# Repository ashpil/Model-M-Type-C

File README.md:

# Model M Type C
This is a project with the simple goal of recreating the old IBM Model M keyboard controller with modern technologies in mind.

## Motivation
Although the IBM Model M is perhaps the most well-known and popular of old keyboards, it isn't equipped with some modern ameneties we have grown used to enjoying. Key features that the Model M lacks are Windows and Media keys(or, broader, firmware-level repogramability), as well as a hotswappable connection with a modern interface. This controller is designed to bring 21st century features to a 20th century keyboard.

## Goals
- Native USB C
- Hotswappable
- Fully configurable with QMK compatibility
- Less power draw
- Complete reversability

## Usage
Note: If your Model M has two ribbon cables with a 16-12 split rather than the three connectors with 16-8-4 split, see [this](https://github.com/ashpil/Model-M-Type-C-Controller/issues/2) issue.

1. Print the board either using a cheap foreign service such as [JLCPBC](https://jlcpcb.com/ "JLCPBC") for around $6 + shipping, or a domestic service such as [OSH Park](https://oshpark.com/ "OSH Park") for around $35. Someone also seems to be selling a PCB for this on eBay, which is totally a scam for $47.95. Does make me feel flattered, though.
2. Order the components- [part list](https://www.digikey.com/short/p00t8f "part list") from Digikey. USB-C port needs to be bought elsewhere, I recommend [here](https://keeb.io/products/usb-c-port-12-pin-hro-type-c-31-m-12 "usb c hro female port").  $15 total for components. If your LEDs connect via a ribbon, get [this](https://www.digikey.com/short/p012jt "this") instead of the JST 4 pin connector. I used [this](https://www.amazon.com/gp/product/B01787RB40 "usb c cable") cable as a riser cable to connect the controller's USB C port to the side of the keyboard. Unfortunately, due to size conflicts, this cannot be done without a riser cable if you want the external usb c cable to be detachable. This brings total component cost to $25 without shipping.
3. Put it together. It's possible to solder these SMD components manually with a soldering iron, but if you are able to find a hot air gun or a reflow oven, it'll be significantly easier. Reference the visual BOM to see what goes where.
4. 3D print the [USB-C cable dock](usbcdock.stl "usb c dock"). You can mount this on top of the board for it to look near-native. Attach the riser cable to the dock with some hot glue or epoxy.
4. Connect the ribbon cables and LED wires, and mount the PCB in the same way the old PCB was mounted. Attach the USB-C dock on top of that.
5. Install firmware.

## Firmware
This board is fully compatible with QMK. This is a default QMK configuration, so all you need to do is run this from your QMK directory when you are ready:

	make ashpil/modelm_usbc:default:flash
	
Check [here](https://github.com/qmk/qmk_firmware/tree/master/keyboards/ashpil/modelm_usbc "QMK profile") for details.

Alternatively you can use the [Vial](https://get.vial.today/) firmware. Setup is analogous to QMK, clone the Vial repo and run:
	
	make ashpil/modelm_usbc:vial:flash

## Other

If you have any problems/comments, or find anything that could be improved, please submit issue or a pull request!

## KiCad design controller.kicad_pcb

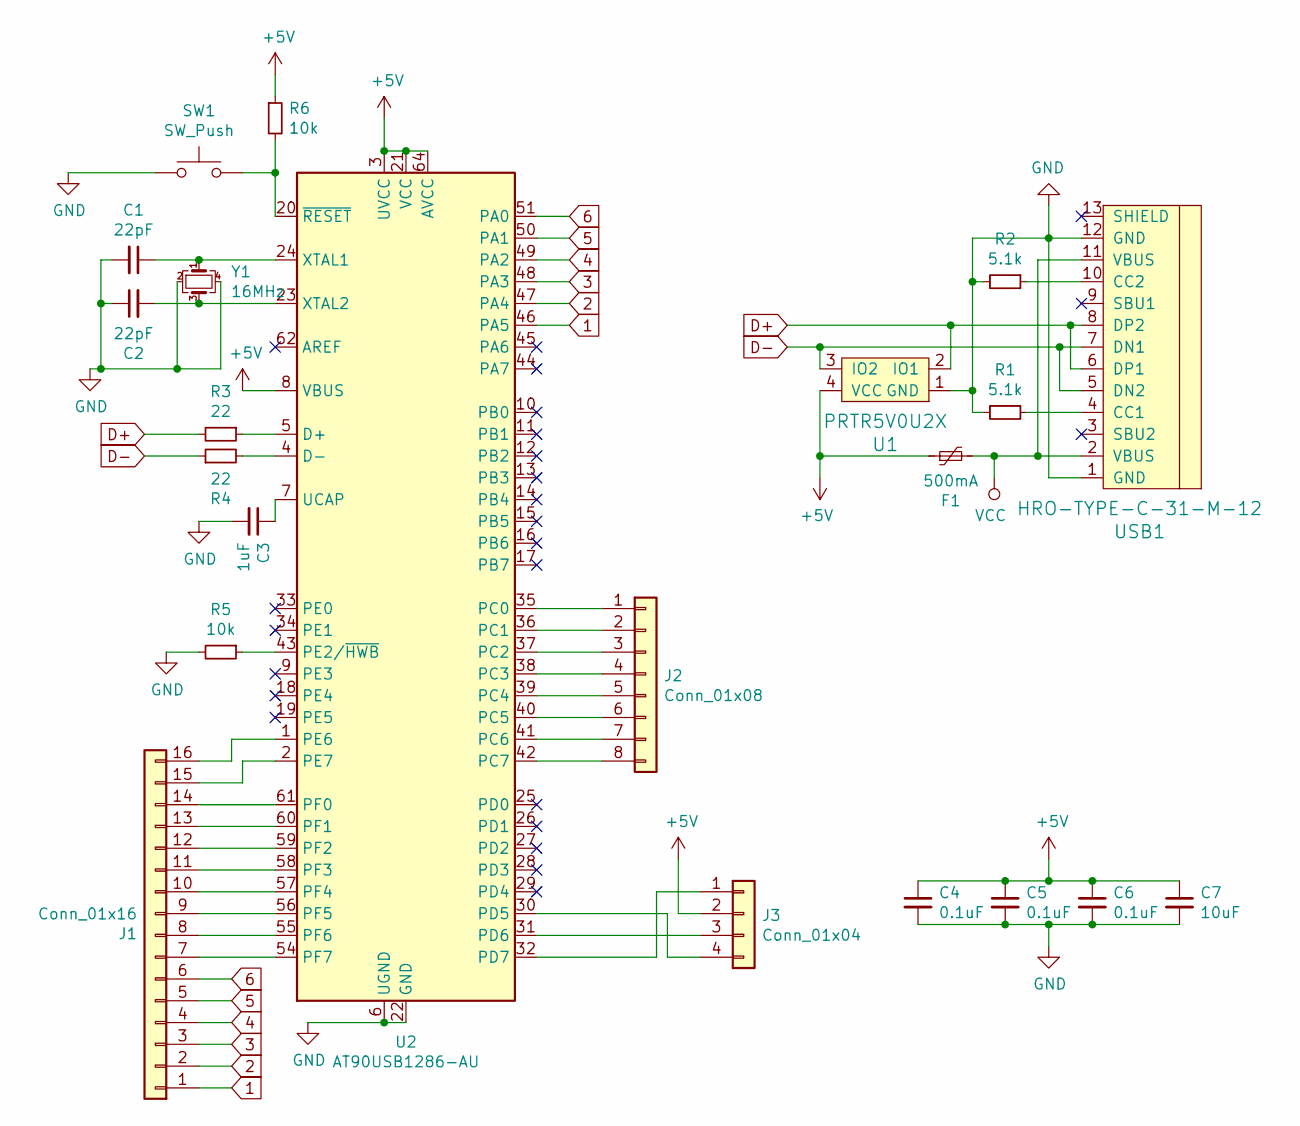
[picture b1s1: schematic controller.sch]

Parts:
C1, C2: 22pF; C_0805_2012Metric
C3: 1uF; C_0805_2012Metric
C4, C5, C6: 0.1uF; C_0805_2012Metric
C7: 10uF; C_0805_2012Metric
F1: 500mA; Fuse_1206_3216Metric
J1: Conn_01x16; PinHeader_1x16_P2.54mm_Vertical
J2: Conn_01x08; PinHeader_1x08_P2.54mm_Vertical
J3: Conn_01x04; PinHeader_1x04_P2.54mm_Vertical
R1, R2: 5.1k; R_0805_2012Metric
R3, R4: 22; R_0805_2012Metric
R5, R6: 10k; R_0805_2012Metric
SW1: SW_Push; SKQG-1155865
U1: PRTR5V0U2X; SOT143B
U2: AT90USB1286-AU; TQFP-64_14x14mm_P0.8mm
USB1: HRO-TYPE-C-31-M-12; HRO-TYPE-C-31-M-12-HandSoldering
Y1: 16MHz; Crystal_SMD_3225-4Pin_3.2x2.5mm

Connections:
1: J1.1, U2.46 (PA5)
2: J1.2, U2.47 (PA4)
3: J1.3, U2.48 (PA3)
4: J1.4, U2.49 (PA2)
5: J1.5, U2.50 (PA1)
6: J1.6, U2.51 (PA0)
+5V: C4.1, C5.1, C6.1, C7.1, F1.1, J3.2, R6.1, U1.4 (VCC), U2.3 (UVCC), U2.8 (VBUS), U2.21 (VCC), U2.52 (VCC), U2.64 (AVCC)
D+: R3.2, U1.2 (IO1), USB1.6 (DP1), USB1.8 (DP2)
D-: R4.1, U1.3 (IO2), USB1.5 (DN2), USB1.7 (DN1)
GND: C1.2, C2.1, C3.2, C4.2, C5.2, C6.2, C7.2, R1.2, R2.2, R5.2, SW1.1, U1.1 (GND), U2.6 (UGND), U2.22 (GND), U2.53 (GND), U2.63 (GND), USB1.1 (GND), USB1.12 (GND), Y1.2, Y1.4
unnamed: C1.1, U2.24 (XTAL1), Y1.1
unnamed: C2.2, U2.23 (XTAL2), Y1.3
unnamed: C3.1, U2.7 (UCAP)
unnamed: J1.7, U2.54 (PF7)
unnamed: J1.8, U2.55 (PF6)
unnamed: J1.9, U2.56 (PF5)
unnamed: J1.10, U2.57 (PF4)
unnamed: J1.11, U2.58 (PF3)
unnamed: J1.12, U2.59 (PF2)
unnamed: J1.13, U2.60 (PF1)
unnamed: J1.14, U2.61 (PF0)
unnamed: J1.15, U2.2 (PE7)
unnamed: J1.16, U2.1 (PE6)
unnamed: J2.1, U2.35 (PC0)
unnamed: J2.2, U2.36 (PC1)
unnamed: J2.3, U2.37 (PC2)
unnamed: J2.4, U2.38 (PC3)
unnamed: J2.5, U2.39 (PC4)
unnamed: J2.6, U2.40 (PC5)
unnamed: J2.7, U2.41 (PC6)
unnamed: J2.8, U2.42 (PC7)
unnamed: J3.1, U2.32 (PD7)
unnamed: J3.3, U2.31 (PD6)
unnamed: J3.4, U2.30 (PD5)
unnamed: R1.1, USB1.4 (CC1)
unnamed: R2.1, USB1.10 (CC2)
unnamed: R3.1, U2.5 (D+)
unnamed: R4.2, U2.4 (D-)
unnamed: R5.1, U2.43 (PE2/~HWB)
unnamed: R6.2, SW1.2, U2.20 (~RESET)
VCC: F1.2, USB1.2 (VBUS), USB1.11 (VBUS)

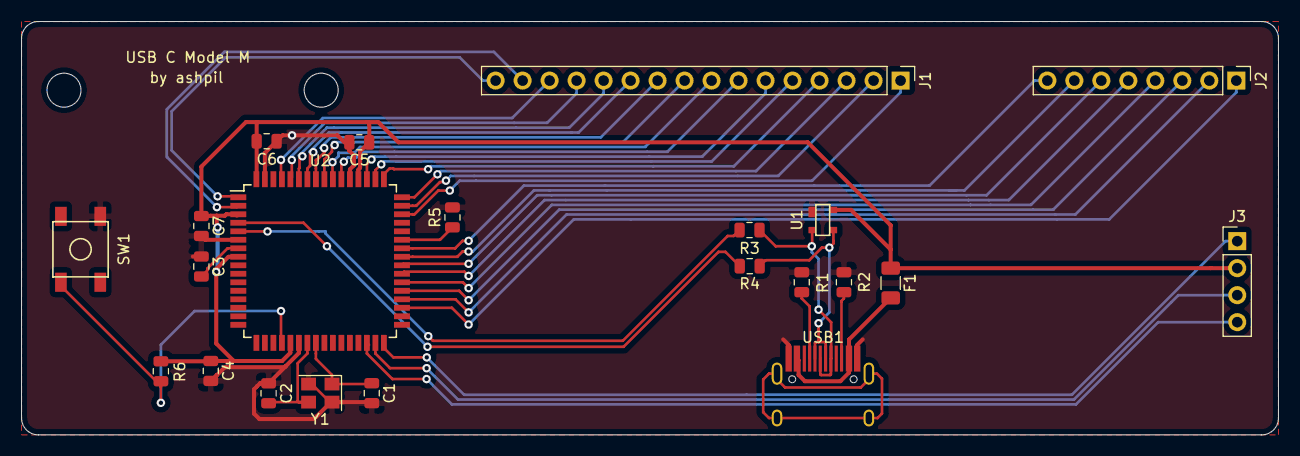
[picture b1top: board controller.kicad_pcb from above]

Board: 2 copper layers, 118.3 x 38.9 mm, 22 parts (0 on the bottom side), 41 nets.

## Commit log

2019-10-29 basic files
2019-10-29 Add submodules
2019-10-29 configuring kicad
2019-10-29 basic schematic and more footprints
2019-10-29 footprints assigned
2019-10-30 changed to at90usb1286 and cleanup
2019-10-30 removed unnecessary module
2019-10-30 add usb-c submodule
2019-10-30 changed to usb c
2019-10-31 pcb design
2019-10-31 completion?! finished all circuitry
2019-10-31 misc tweaks for shield and usb pathing
2019-10-31 clarified resistor value
2019-10-31 made gound/5v/usb routing neater
2019-10-31 generated gerbers
2019-11-01 part list added
2019-11-15 rev 2
    Adjusted ucb-c location, fixed grounding error, changed some sizes to be more snug
2019-11-16 fixed LED connector
2019-11-16 final touches, cleanup
2019-11-16 pictures!
2019-11-16 readme and fix
2019-11-16 readme
2019-11-17 updated readme and fixes
2019-11-17 update license
2019-11-17 added TODO
2019-11-17 fixed readme
2019-11-21 updated images and instructions to include 3d print
2019-11-27 new images and updated readme
2020-01-28 Update .gitattributes
    Fixed language issue
2020-01-28 Update .gitattributes
    Actually fixed language
2020-09-24 add warning about ebay to readme
2020-10-05 adds gitignore
2020-10-05 removes unneeded files
2020-10-28 updates submodules
2023-05-26 Add Vial Note
